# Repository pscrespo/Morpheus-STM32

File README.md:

# Morpheus-STM32 (work in progress)
A cheap 3D printer controller board for use with a "Blue Pill" STM32F1 generic board. Inspired on http://reprap.org/wiki/SinapTec

Design goals:
---------------

 - Follow the [KISS Principle](https://en.wikipedia.org/wiki/KISS_principle)
 - Low cost
 - Single layer copper board
 - DIY-able (easy to make via toner transfer)
 - Only through-hole components
 - The very basic a printer would need
   - Keep bed circuit separated/optional (if you are making a PLA only printer without a heated bed, you don't need to populate the bed circuit zone)
 - Open Source Hardware, made in Open Source Software

Features:
---------------

 - 4 Pololu-like steppers (X, Y, Z, E0)
 - 3 mosfets (Hotend heater, print cooling fan and bed heater)
 - 3 MIN endstops (X, Y, Z)
 - Z Probe pin (in case you are building a delta printer and need the extra endstop)
 - 2 thermistors (for E0 and bed)
 - 2 12V fan connectors
 - I2C and SPI header
  
 # WARNING:
 - All logic voltage in this board is 3.3V. Do not connect 5V logic addons/devices without proper level adapting.
 - ~This board has no reverse current protection,~ it has a diode to short-circuit and protect the board in case of reverse current, but if you connect power incorrectly you'll still damage components and/or your power supply (there's also a risk of caching fire, so please be careful).
 - This board has no overcurrent protection, please use a fuse on power input (e.g. auto-blade or inline fuse holder), recommended values are of 5A for the main board and 10A for the bed circuit.
 - Check all connections before plugging power.
 - Now for real, check connections...
 
 Notes:
 ---------------
 - Usually, "blue pill" boards have a wrong R10 value (USB pullpup resistor, should be 1.5k but manufcturers place a 10k or other value resistor instead), so you can add a 1.8k in R13. If your board has the correct value or you already fixed it in the board, then leave R13 unpopulated.
 - ~Hotend sensor uses a 1k resistor pullup (R1). Anyway, if you're having trouble with finding (or creating) thermistor tables, just replace it with a 4.7k resistor and use the usual Marlin tables.~ 
  Now Marlin has configurable thermistors, you can use thermistor **1000** in **configuration.h** and choose pull-up, ressistance and beta values in **configuration_adv.h**

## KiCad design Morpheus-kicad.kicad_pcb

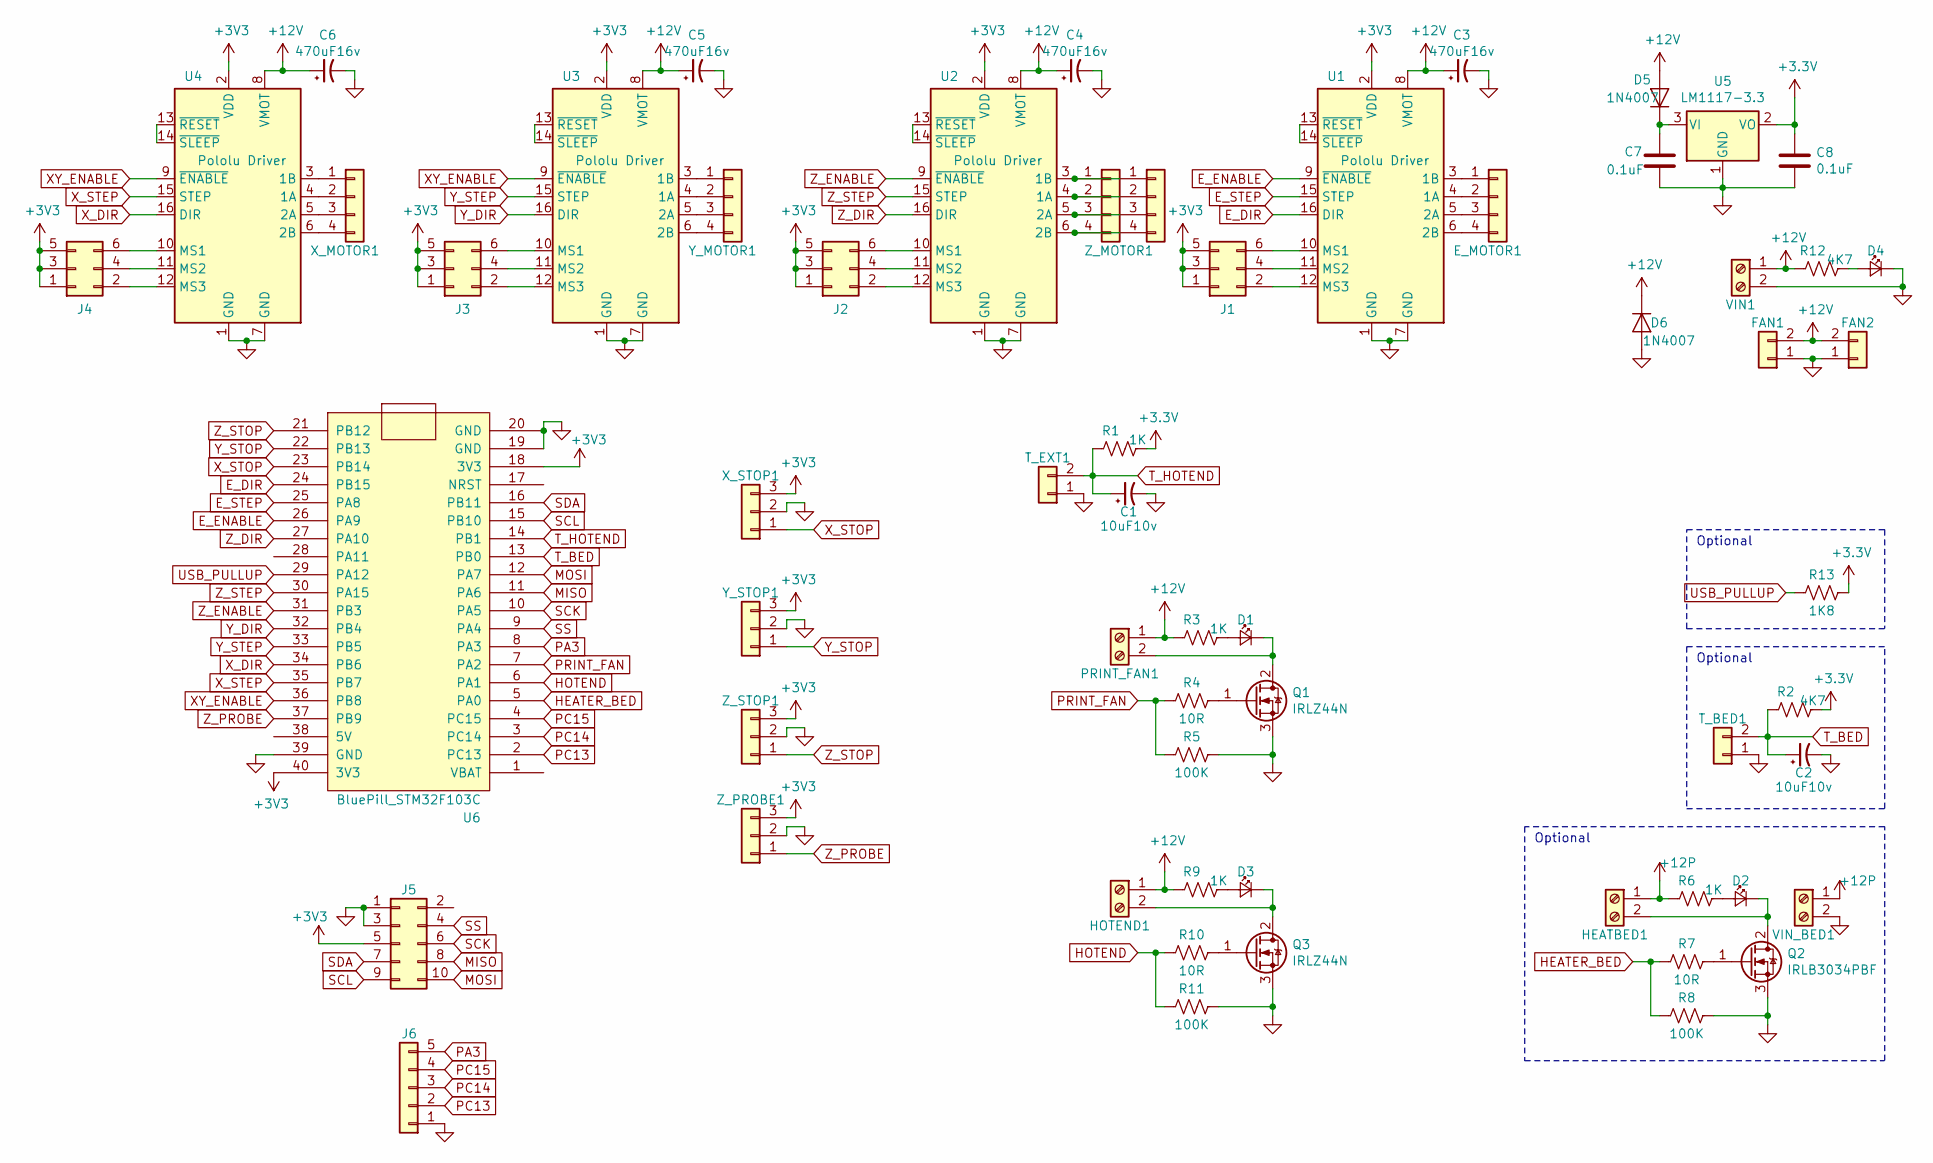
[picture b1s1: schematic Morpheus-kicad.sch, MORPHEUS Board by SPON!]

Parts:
C1, C2: 10uF10v; CP_Radial_D5.0mm_P2.00mm
C3, C4, C5, C6: 470uF16v; CP_Radial_D8.0mm_P3.80mm
C7, C8: 0.1uF; C_Disc_D3.4mm_W2.1mm_P2.50mm
D1, D2, D3: LED_Small; LED_D3.0mm
D4: LED_Small; LED_D3.0mm_Clear
D5: 1N4007; D_DO-35_SOD27_P7.62mm_Horizontal
D6: 1N4007; D_DO-35_SOD27_P2.54mm_Vertical_AnodeUp
E_MOTOR1: E_MOTOR; PinHeader_1x04_P2.54mm_Vertical
FAN1, FAN2: Conn_01x02; PinHeader_1x02_P2.54mm_Vertical
HEATBED1: HEATBED; TerminalBlock_Phoenix_MKDS-1,5-2_1x02_P5.00mm_Horizontal
HOTEND1: HOTEND; TerminalBlock_Phoenix_MKDS-1,5-2_1x02_P5.00mm_Horizontal
J1, J2, J3, J4: Conn_02x03_Odd_Even; PinHeader_2x03_P2.54mm_Vertical
J5: Conn_02x05_Counter_Clockwise; PinHeader_2x05_P2.54mm_Vertical
J6: Conn_01x05; PinHeader_1x05_P2.54mm_Vertical
PRINT_FAN1: PRINT_FAN; TerminalBlock_Phoenix_MKDS-1,5-2_1x02_P5.00mm_Horizontal
Q1, Q3: IRLZ44N; TO-220-3_Vertical
Q2: IRLB3034PBF; TO-220-3_Vertical
R1, R3, R6, R9: 1K; R_Axial_DIN0207_L6.3mm_D2.5mm_P7.62mm_Horizontal
R2, R12: 4K7; R_Axial_DIN0207_L6.3mm_D2.5mm_P7.62mm_Horizontal
R4, R7, R10: 10R; R_Axial_DIN0207_L6.3mm_D2.5mm_P7.62mm_Horizontal
R5, R8, R11: 100K; R_Axial_DIN0207_L6.3mm_D2.5mm_P7.62mm_Horizontal
R13: 1K8; R_Axial_DIN0207_L6.3mm_D2.5mm_P7.62mm_Horizontal
T_BED1: T_BED; PinHeader_1x02_P2.54mm_Vertical
T_EXT1: T_EXT; PinHeader_1x02_P2.54mm_Vertical
U1, U2, U3, U4: Pololu Driver; Pololu_Breakout-16_15.2x20.3mm
U5: LM1117-3.3; TO-220-3_Vertical
U6: BluePill_STM32F103C
VIN1: VIN; TerminalBlock_Phoenix_MKDS-1,5-2_1x02_P5.00mm_Horizontal
VIN_BED1: VIN_BED; TerminalBlock_Phoenix_MKDS-1,5-2_1x02_P5.00mm_Horizontal
X_MOTOR1: X_MOTOR; PinHeader_1x04_P2.54mm_Vertical
X_STOP1: X_STOP; PinHeader_1x03_P2.54mm_Vertical
Y_MOTOR1: Y_MOTOR; PinHeader_1x04_P2.54mm_Vertical
Y_STOP1: Y_STOP; PinHeader_1x03_P2.54mm_Vertical
Z_MOTOR1: Z_MOTOR; PinHeader_1x04_P2.54mm_Vertical
Z_MOTOR2: Conn_01x04; PinHeader_1x04_P2.54mm_Vertical
Z_PROBE1: Z_PROBE; PinHeader_1x03_P2.54mm_Vertical
Z_STOP1: Z_STOP; PinHeader_1x03_P2.54mm_Vertical

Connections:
+12P: HEATBED1.1, R6.2, VIN_BED1.1
+12V: C3.1, C4.1, C5.1, C6.1, D5.2 (A), D6.1 (K), FAN1.2, FAN2.2, HOTEND1.1, PRINT_FAN1.1, R3.2, R9.2, R12.2, U1.8 (VMOT), U2.8 (VMOT), U3.8 (VMOT), U4.8 (VMOT), VIN1.1
E_DIR: U1.16 (DIR), U6.24 (PB15)
E_ENABLE: U1.9 (~ENABLE), U6.26 (PA9)
E_STEP: U1.15 (STEP), U6.25 (PA8)
GND: C1.2, C2.2, C3.2, C4.2, C5.2, C6.2, C7.2, C8.2, D4.1 (K), D6.2 (A), FAN1.1, FAN2.1, J5.1, J5.3, J6.1, Q1.3 (S), Q2.3 (S), Q3.3 (S), R5.1, R8.1, R11.1, T_BED1.1, T_EXT1.1, U1.1 (GND), U1.7 (GND), U2.1 (GND), U2.7 (GND), U3.1 (GND), U3.7 (GND), U4.1 (GND), U4.7 (GND), U5.1 (GND), U6.19 (GND), U6.20 (GND), U6.39 (GND), VIN1.2, VIN_BED1.2, X_STOP1.2, Y_STOP1.2, Z_PROBE1.2, Z_STOP1.2
HEATER_BED: R7.2, R8.2, U6.5 (PA0)
HOTEND: R10.2, R11.2, U6.6 (PA1)
MISO: J5.8, U6.11 (PA6)
MOSI: J5.10, U6.12 (PA7)
unnamed: C7.1, D5.1 (K), U5.3 (VI)
unnamed: D1.1 (K), PRINT_FAN1.2, Q1.2 (D)
unnamed: D1.2 (A), R3.1
unnamed: D2.1 (K), HEATBED1.2, Q2.2 (D)
unnamed: D2.2 (A), R6.1
unnamed: D3.1 (K), HOTEND1.2, Q3.2 (D)
unnamed: D3.2 (A), R9.1
unnamed: D4.2 (A), R12.1
unnamed: E_MOTOR1.1, U1.3 (1B)
unnamed: E_MOTOR1.2, U1.4 (1A)
unnamed: E_MOTOR1.3, U1.5 (2A)
unnamed: E_MOTOR1.4, U1.6 (2B)
unnamed: J1.2, U1.12 (MS3)
unnamed: J1.4, U1.11 (MS2)
unnamed: J1.6, U1.10 (MS1)
unnamed: J2.2, U2.12 (MS3)
unnamed: J2.4, U2.11 (MS2)
unnamed: J2.6, U2.10 (MS1)
unnamed: J3.2, U3.12 (MS3)
unnamed: J3.4, U3.11 (MS2)
unnamed: J3.6, U3.10 (MS1)
unnamed: J4.2, U4.12 (MS3)
unnamed: J4.4, U4.11 (MS2)
unnamed: J4.6, U4.10 (MS1)
unnamed: Q1.1 (G), R4.1
unnamed: Q2.1 (G), R7.1
unnamed: Q3.1 (G), R10.1
unnamed: U1.13 (~RESET), U1.14 (~SLEEP)
unnamed: U2.3 (1B), Z_MOTOR1.1, Z_MOTOR2.1
unnamed: U2.4 (1A), Z_MOTOR1.2, Z_MOTOR2.2
unnamed: U2.5 (2A), Z_MOTOR1.3, Z_MOTOR2.3
unnamed: U2.6 (2B), Z_MOTOR1.4, Z_MOTOR2.4
unnamed: U2.13 (~RESET), U2.14 (~SLEEP)
unnamed: U3.3 (1B), Y_MOTOR1.1
unnamed: U3.4 (1A), Y_MOTOR1.2
unnamed: U3.5 (2A), Y_MOTOR1.3
unnamed: U3.6 (2B), Y_MOTOR1.4
unnamed: U3.13 (~RESET), U3.14 (~SLEEP)
unnamed: U4.3 (1B), X_MOTOR1.1
unnamed: U4.4 (1A), X_MOTOR1.2
unnamed: U4.5 (2A), X_MOTOR1.3
unnamed: U4.6 (2B), X_MOTOR1.4
unnamed: U4.13 (~RESET), U4.14 (~SLEEP)
PA3: J6.5, U6.8 (PA3)
PC13: J6.2, U6.2 (PC13)
PC14: J6.3, U6.3 (PC14)
PC15: J6.4, U6.4 (PC15)
PRINT_FAN: R4.2, R5.2, U6.7 (PA2)
SCK: J5.6, U6.10 (PA5)
SCL: J5.9, U6.15 (PB10)
SDA: J5.7, U6.16 (PB11)
SS: J5.4, U6.9 (PA4)
T_BED: C2.1, R2.2, T_BED1.2, U6.13 (PB0)
T_HOTEND: C1.1, R1.2, T_EXT1.2, U6.14 (PB1)
USB_PULLUP: R13.2, U6.29 (PA12)
XY_ENABLE: U3.9 (~ENABLE), U4.9 (~ENABLE), U6.36 (PB8)
X_DIR: U4.16 (DIR), U6.34 (PB6)
X_STEP: U4.15 (STEP), U6.35 (PB7)
X_STOP: U6.23 (PB14), X_STOP1.1
Y_DIR: U3.16 (DIR), U6.32 (PB4)
Y_STEP: U3.15 (STEP), U6.33 (PB5)
Y_STOP: U6.22 (PB13), Y_STOP1.1
Z_DIR: U2.16 (DIR), U6.27 (PA10)
Z_ENABLE: U2.9 (~ENABLE), U6.31 (PB3)
Z_PROBE: U6.37 (PB9), Z_PROBE1.1
Z_STEP: U2.15 (STEP), U6.30 (PA15)
Z_STOP: U6.21 (PB12), Z_STOP1.1

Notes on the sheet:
Optional

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
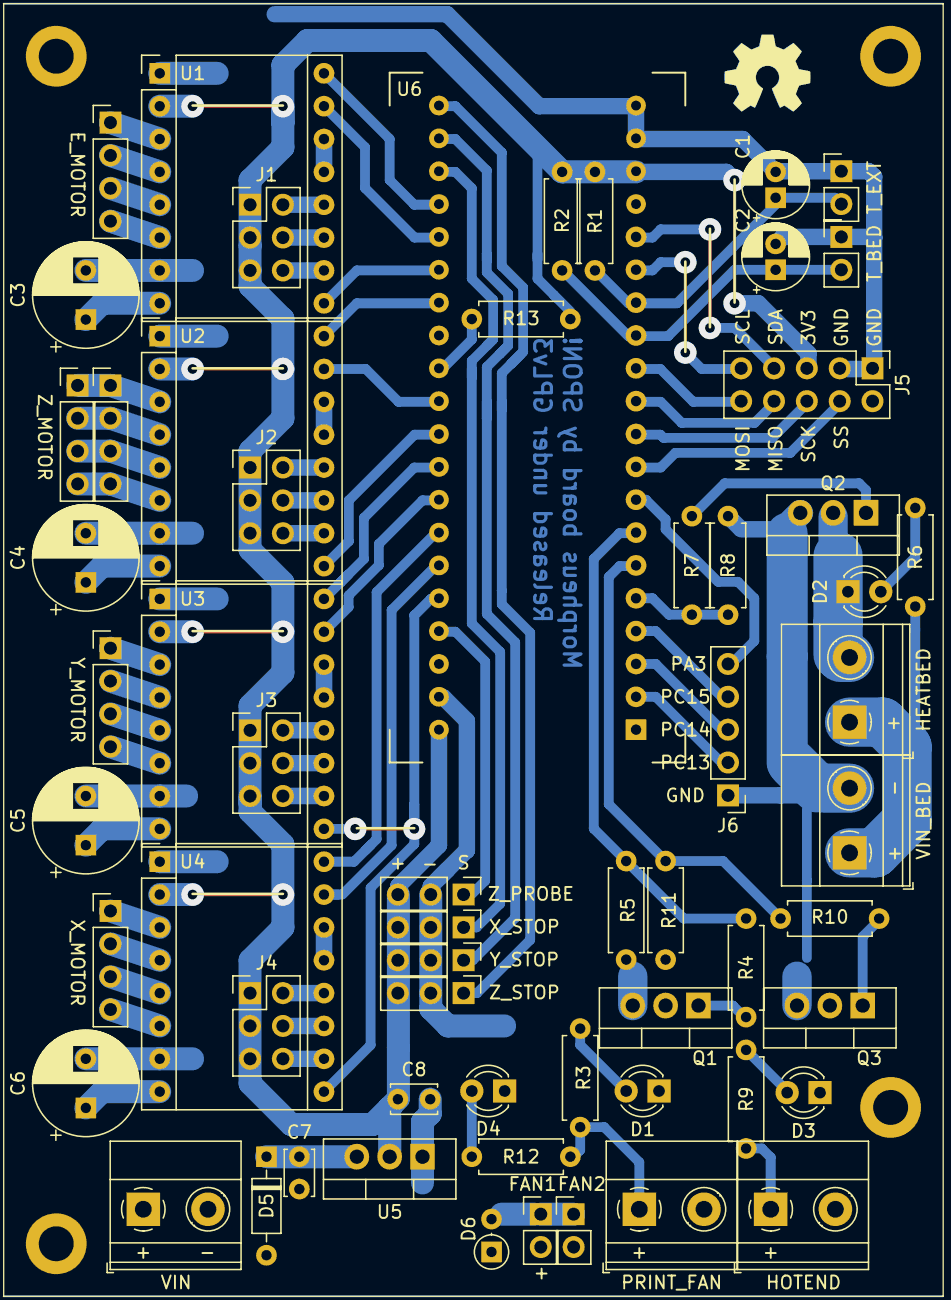
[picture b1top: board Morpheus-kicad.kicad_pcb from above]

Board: 2 copper layers, 60 parts (0 on the bottom side), 78 nets.

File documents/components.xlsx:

Reference | Quantity | Value | Footprint | Notes
C1 C2 | 2 | 10uF10v | Capacitor_THT:CP_Radial_D5.0mm_P2.00mm
C3 C4 C5 C6 | 4 | 470uF16v | Capacitor_THT:CP_Radial_D8.0mm_P3.80mm
C7 C8 | 2 | 0.1uF | Capacitor_THT:C_Disc_D3.4mm_W2.1mm_P2.50mm
D1 D2 D3 | 3 | LED 3mm (Red) | LED_THT:LED_D3.0mm
D4 | 1 | LED 3mm (Green) | LED_THT:LED_D3.0mm_Clear
D5 | 1 | 1N4007 | Diode_THT:D_DO-35_SOD27_P7.62mm_Horizontal
HEATBED1 HOTEND1 PRINT_FAN1 VIN1 VIN_BED1 | 5 | Phoenix MKDS-1,5 2pin | TerminalBlock_Phoenix:TerminalBlock_Phoenix_MKDS-1,5-2_1x02_P5.00mm_Horizontal
Q1 Q3 | 2 | IRLZ44N | Package_TO_SOT_THT:TO-220-3_Vertical
Q2 | 1 | IRLB3034PBF | Package_TO_SOT_THT:TO-220-3_Vertical
R1 R3 R6 R9 | 4 | 1K | Resistor_THT:R_Axial_DIN0207_L6.3mm_D2.5mm_P7.62mm_Horizontal
R12 R2 | 2 | 4K7 | Resistor_THT:R_Axial_DIN0207_L6.3mm_D2.5mm_P7.62mm_Horizontal
R13 | 1 | 1K8 | Resistor_THT:R_Axial_DIN0207_L6.3mm_D2.5mm_P7.62mm_Horizontal | May be a different value for your bluepill, or not even needed.
R10 R4 R7 | 3 | 10R | Resistor_THT:R_Axial_DIN0207_L6.3mm_D2.5mm_P7.62mm_Horizontal
R11 R5 R8 | 3 | 100K | Resistor_THT:R_Axial_DIN0207_L6.3mm_D2.5mm_P7.62mm_Horizontal
T_BED1 T_EXT1 FAN1 FAN2 | 4 | Male header 01x02 | Connector_PinHeader_2.54mm:PinHeader_1x02_P2.54mm_Vertical | There are 74 pins in total, so you need 2 40pin header strips.
J1 J2 J3 J4 | 4 | Male header 02x03 | Connector_PinHeader_2.54mm:PinHeader_2x03_P2.54mm_Vertical
J5 | 1 | Male header 02x05 | Connector_PinHeader_2.54mm:PinHeader_2x05_P2.54mm_Vertical
X_STOP1 Y_STOP1 Z_STOP1 Z_PROBE1 | 4 | Male header 01x03 | Connector_PinHeader_2.54mm:PinHeader_1x03_P2.54mm_Vertical
X_MOTOR1 Y_MOTOR1 Z_MOTOR1 Z_MOTOR2 E_MOTOR1 | 5 | Male header 01x04 | Connector_PinHeader_2.54mm:PinHeader_1x04_P2.54mm_Vertical
U1 U2 U3 U4 | 4 | Pololu Driver | Module:Pololu_Breakout-16_15.2x20.3mm | This would be 4 40pin female header strips, but you can get away with 3.
U6 | 1 | BluePill_STM32F103C | Footprint based on the one made by www.rogerclark.net
U5 | 1 | LM1117-3.3 | Package_TO_SOT_THT:TO-220-3_Vertical | Consider using a heatsink for this.

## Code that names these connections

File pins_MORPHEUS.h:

/**
 * Marlin 3D Printer Firmware
 * Copyright (C) 2019 MarlinFirmware [https://github.com/MarlinFirmware/Marlin]
 *
 * Based on Sprinter and grbl.
 * Copyright (C) 2011 Camiel Gubbels / Erik van der Zalm
 *
 * This program is free software: you can redistribute it and/or modify
 * it under the terms of the GNU General Public License as published by
 * the Free Software Foundation, either version 3 of the License, or
 * (at your option) any later version.
 *
 * This program is distributed in the hope that it will be useful,
 * but WITHOUT ANY WARRANTY; without even the implied warranty of
 * MERCHANTABILITY or FITNESS FOR A PARTICULAR PURPOSE.  See the
 * GNU General Public License for more details.
 *
 * You should have received a copy of the GNU General Public License
 * along with this program.  If not, see <http://www.gnu.org/licenses/>.
 *
 */

 /**
  * 2017 Victor Perez Marlin for stm32f1 test
  * 2018 Modified by Pablo Crespo for Morpheus Board (https://github.com/pscrespo/Morpheus-STM32)
  */

/**
 * MORPHEUS Board pin assignments
 */

#ifndef __STM32F1__
  #error "Oops! Select an STM32F1 board in 'Tools > Board.'"
#endif

#define BOARD_NAME "Bluepill based board"

//
// Limit Switches
//
#define X_STOP_PIN         PB14
#define Y_STOP_PIN         PB13
#define Z_STOP_PIN         PB12

//
// Z Probe
//
#define Z_MIN_PROBE_PIN    PB9

//
// Steppers
//
// X & Y enable are the same
#define X_STEP_PIN         PB7
#define X_DIR_PIN          PB6
#define X_ENABLE_PIN       PB8

#define Y_STEP_PIN         PB5
#define Y_DIR_PIN          PB4
#define Y_ENABLE_PIN       PB8

#define Z_STEP_PIN         PA15
#define Z_DIR_PIN          PA10
#define Z_ENABLE_PIN       PB3

#define E0_STEP_PIN        PA8
#define E0_DIR_PIN         PB15
#define E0_ENABLE_PIN      PA9

//
// Temperature Sensors
//
#define TEMP_0_PIN         PB1   // Analog Input (HOTEND thermistor)
#define TEMP_BED_PIN       PB0   // Analog Input (BED thermistor)

//
// Heaters / Fans
//
#define HEATER_0_PIN       PA1   // HOTEND MOSFET
#define HEATER_BED_PIN     PA0   // BED MOSFET

#define FAN_PIN            PA2   // PRINT FAN

//
// Misc.
//
#define SDSS               PA3
#define SD_DETECT_PIN      -1
#define LED_PIN            PC13
#define DISABLE_JTAG
#define FAN_SOFT_PWM

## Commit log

2017-09-27 Initial release
2017-09-28 More descriptive Readme
2017-09-28 More descriptive Readme file
2017-10-02 Changed screw terminal footprints
    Changed screw terminal footprints, added silk lines to bridges, re-arranged bed circuit
2017-10-02 Added fan 12v connectors
    Added 2 fan connectors, one for extruder and an optional one for cooling the board.
2017-10-02 Update images
2017-10-09 Added I2C and SPI Header
    Added connector for external addons, which can use SPI and second I2C bus. Also updated readme file.
2017-10-10 Added Z-probe and experimental pins.h file
    Added Z-probe (very useful in delta printers) and a basic pins.h file for experimenting with Marlin Firmware.
2018-01-16 Caps corrected
    Corrected driver's capacitors to right size.
    Added OSHW logo :)
2018-05-18 Modify Readme file
    Added warnings and reformatted.
2018-05-18 Change Z-Probe pin
    X and Y enable now share the same pin.
    Z probe has a new pin.
    Reformatted pin definition file.
2018-05-18 Reorganized documents and created PDF files for toner transfer
2018-05-18 Updated preview
2018-05-23 Update readme file
2018-05-23 Add an optional resistor to fix R10 value on bluepill, as documented on http://wiki.stm32duino.com/index.php?title=Blue_Pill
2018-08-26 Various changes
    Squeezed board length so it's 10cm long.
    Added polarity indicators to headers.
    Changed name of screw terminals.
    Added diode to LM1117 input.
    Added SDSS pin.
2018-08-26 New version
    Update documents.
2019-01-25 Prepare branch for (coming soon) KiCAD rework.
2019-07-12 Update texts
    Update readme and pins file for v0.4.
2019-07-12 Add KiCAD based version
    Add KiCAD based version. Hopefully this will allow people to modify the board easier than with gEDA.
2019-07-12 Add documents
    Add the usual templates for etching the board, plus BOM, schematics and render pictures.
2019-08-14 Add reverse current protection
    Added a 1N4007 or similar diode to protect from reverse current. Bear in mind that, without a fuse, it will just burn and let current pass again, damaging components.
2019-08-14 Update readme
    Added reverse current protection. Also, Marlin (2.0) has a new feature in which you can set thermistor values directly, so a new table isn't needed.
2019-11-20 Add header
    Added a header for the unused pins, just to make them usable.
2020-04-16 Modified headers and added teardrops
    Re-organized J5 and J6 headers, and added teardrops on all pads, which helps a lot with home etching.
    Also, after seeing some people who needed an external USB port, I added a small header to take out the USB data lines without changing the whole board.

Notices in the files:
Morpheus-kicad.kicad_pcb:
Released under GPLv3
